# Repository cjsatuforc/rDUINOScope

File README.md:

# rDUINOScope

### ILI9488 3.5" SPI version: [buy pre-assembled kit](https://giacu92.bigcartel.com/product/rduinoscope-ili9488)
This rDUINOScope is an enanched version of the main release. The main differences are the following:

-  Uses ILI9488 480x320 px display in SPI, instead of HX8352B 400x240 px display, so bigger screen and less pin used. You can get a pre-assembled version in my [bigcartel shop](https://giacu92.bigcartel.com/product/rduinoscope-ili9488) or get yourself the 
ILI9488 display alone: [https://www.buydisplay.com/default/serial-spi-3-5-inch-tft-lcd-module-in-320x480-optl-touchscreen-ili9488](https://www.buydisplay.com/default/serial-spi-3-5-inch-tft-lcd-module-in-320x480-optl-touchscreen-ili9488)
-  Using AD7873 touch IC. Also compatibile with TSC2046/XPT2046 and ADS7843/AD7843 ICs. The software is able to detect and display any communications error with the touch IC.
-  Small code optimization to maximize speed (the ILI9488 supports only 24bit/px so it's quite slow as screen compared to HX... ones).
-  Joypad calibration at startup. No more panic to find the right values for the joypad.
-  Empirial March sound function moved to confirm good initialization of the device. If no sound then you're having problems! :'(
-  Automatic data and time set on clockScreen() derived from GPS data: the software is able to calculate the location's time zone and to auto update from summer or winter time.
-  Custom line of text can be appended to any .csv file to display custom "Description" strings. Example: I added "rich cluster with more than 100 stars" to M11 in messier.csv.
-  Changed color for Name and Description when tracking objects.
-  Different pin arrangement.
-  Options page settings such as tft brightness or sound state, are now saved onto the SD card and restored at each boot.
-  Added custom.csv wich can be used to add more custom sky objects.
-  Added pictures of all objects when tracking.

New features in development:
===========================================================
- Onboard touchscreen calibration
- Solar system objects tracking

## THE WORLD'S FIRST STAND ALONE ARDUINO BASED TELESCOPE CONTROL GOTO (handheld controller). 

rDUINOScope is an Open Source, Arduino Due based Telescope Control System (GOTO). Drafted as stand alone system, rDUINOScope does not need PC, Tablet or Cell Phone, nor Internet connection in order to operate and deliver stunning views! It does however supports Bluetooth and LX200 protocol to connect and be controlled by smart devices!

rDUINOScope uses database with THE BEST ~250 stellar objects ( Messier and Hidden Treasures Catalogues) and 200 stars, calculates their position on the sky and points the telescope. Implemented Alignment procedures allow for "Always in the eyepiece" experience when slewing to selected objects and once the object is in the eyepiece, the system keeps tracking it.

The best part of rDUINOScope is that it is an OPEN SOURCE SOFTWARE and HARDWARE! Few custom telescope makers have announced that they are adding or about to add it to their product line. In addition, few months ago a new HW shield board was born as a spin-off project to spare you the hassle of building your own rDUINOScope!

Published under GNU General Public License

Instructions on how to build hardware can be found on the project's website: http://rduinoscope.byethost24.com/
HACKADAY.IO Project: https://hackaday.io/project/21024-rduinoscope

Facebook: https://www.facebook.com/rDUINOScope/

# rDUINOScope _2.3.1_Boiana_EQ_Giacomo
===========================================================
Release date: 03 August 2017
Status: Stable Version
Author: Dessislav Gouzgounov / Десислав Гузгнов /(deskog@gmail.com) 
Edited: Giacomo Mammarella (giacomo.mammarella@student.univaq.it)

v2.3.1 aims to bring all existing hardware platforms into one code base. Additionally this version introduces new features to the rDUINOScope like Screensaver, TFT brightness, MosFET to control power to DRV8825 and etc.

Current release will also be used as a base to add the Alt/Az changes.

New features added in v2.3.1:
===========================================================
- Brings all existing flavours of the hardware to use same code!
- Hardware Changes!!! - Plese reffer to the HACKADAY instructions!
- Screen Brightness control;
- Screen Auto OFF function with timeout;
- Implemented FET transistor to control power to the stepper motors;
- More BlueTooth commands added to prepare for a screenless version (or operation);
- It is now possible to control rDUINOScope without the TFT screen - so called "BLIND" version.
- BUG fixes:
	- GPS fixes;
	- SlewTo speed issues for low amperage;

New features added in v2.3:
===========================================================
- Code Optimization for Performance (SlewTo now capable of speeds > 3 deg/sec);
- Added Celestial, Lunar and Solar tracking speeds;
- Added new Main Menu system for more functionality;
- Added control on 2 external devices (DEV 1 & 2 - you can hook your Heater, Fan and etc);
- Added support for SkySafari 5 (smartphone software);
- Added build in Star Atlas showing current telescope position;
- Shows current Firmware version on Loading screen and on Bluetooth request using LX200 protocol;
- Bug fixes:
	o Wrong DEC movement for negative DEC values passed over Bluetooth;
	o LST revised in the format XX:XX;

New features added in v2.1:
===========================================================
- Added “1 Star Alignment” Method;
- Added “Iterative Alignment” Method;
- Added 200 brightest stars to be used in alignment procedures;
- Added Bluetooth control from Stellarium (cloned LX200 communication protocols);
- Added Bluetooth connection with PC;
- Code has been refactored for easy reading/editing;
- Bug fixes:
	o Wrong DEC movement for negative DEC values;
	o Revised RA movement formula;
	o OnScreen messages have been fixed;
	o 1px. Buttons move after press event was fixed;

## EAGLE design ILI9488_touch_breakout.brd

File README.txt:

#rDUINOScope

ILI9488 SPI version:
	- Empirial March sound function moved after good initialization of the device.
      	- Auto data and time settings on clockScreen from GPS data: the software is able to calculate the location's time zone and to auto update to summer or winter time.
      	- Using AD7873 touch IC. Also compatibile with TSC2046/XPT2046 and ADS7843/AD7843 ICs. The software is able to detect and display any communications error with the touch IC.
	- Custom line of text can be appended to any .csv file to display custom "Description" strings. Example: I added "rich cluster with more than 100 stars" to M11 in messier.csv
      	- Changed color for Name and Description when tracking objects.
   	- Different pin arrangement
      	- Added custom.csv wich can be used to add more custom sky objects (still to be implemented)

THE WORLD'S FIRST STAND ALONE ARDUINO BASED TELESCOPE CONTROL GOTO (handheld controller). 

rDUINOScope is an Open Source, Arduino Due based Telescope Control System (GOTO). Drafted as stand alone system, rDUINOScope does not need PC, Tablet or Cell Phone, nor Internet connection in order to operate and deliver stunning views! It does however supports Bluetooth and LX200 protocol to connect and be controlled by smart devices!

rDUINOScope uses database with THE BEST ~250 stellar objects ( Messier and Hidden Treasures Catalogues) and 200 stars, calculates their position on the sky and points the telescope. Implemented Alignment procedures allow for "Always in the eyepiece" experience when slewing to selected objects and once the object is in the eyepiece, the system keeps tracking it.

The best part of rDUINOScope is that it is an OPEN SOURCE SOFTWARE and HARDWARE! Few custom telescope makers have announced that they are adding or about to add it to their product line. In addition, few months ago a new HW shield board was born as a spin-off project to spare you the hassle of building your own rDUINOScope!

Published under GNU General Public License

Instructions on how to build hardware can be found on the project's website: http://rduinoscope.byethost24.com/
HACKADAY.IO Project: https://hackaday.io/project/21024-rduinoscope

Facebook: https://www.facebook.com/rDUINOScope/

#rDUINOScope _2.3.1_Boiana_EQ_Giacomo
===========================================================
Release date: 03 August 2017
Status: Stable Version
Author: Dessislav Gouzgounov / Десислав Гузгнов /(deskog@gmail.com) 
Edited: Giacomo Mammarella (mammarella.g@gmail.com)

v2.3.1 aims to bring all existing hardware platforms into one code base. Additionally this version introduces new features to the rDUINOScope like Screensaver, TFT brightness, MosFET to control power to DRV8825 and etc.

Current release will also be used as a base to add the Alt/Az changes.

New features added in v2.3.1:
===========================================================
- Brings all existing flavours of the hardware to use same code!
- Hardware Changes!!! - Plese reffer to the HACKADAY instructions!
- Screen Brightness control;
- Screen Auto OFF function with timeout;
- Implemented FET transistor to control power to the stepper motors;
- More BlueTooth commands added to prepare for a screenless version (or operation);
- It is now possible to control rDUINOScope without the TFT screen - so called "BLIND" version.
- BUG fixes:
	- GPS fixes;
	- SlewTo speed issues for low amperage;

New features added in v2.3:
===========================================================
- Code Optimization for Performance (SlewTo now capable of speeds > 3 deg/sec);
- Added Celestial, Lunar and Solar tracking speeds;
- Added new Main Menu system for more functionality;
- Added control on 2 external devices (DEV 1 & 2 - you can hook your Heater, Fan and etc);
- Added support for SkySafari 5 (smartphone software);
- Added build in Star Atlas showing current telescope position;
- Shows current Firmware version on Loading screen and on Bluetooth request using LX200 protocol;
- Bug fixes:
	o Wrong DEC movement for negative DEC values passed over Bluetooth;
	o LST revised in the format XX:XX;

New features added in v2.1:
===========================================================
- Added “1 Star Alignment” Method;
- Added “Iterative Alignment” Method;
- Added 200 brightest stars to be used in alignment procedures;
- Added Bluetooth control from Stellarium (cloned LX200 communication protocols);
- Added Bluetooth connection with PC;
- Code has been refactored for easy reading/editing;
- Bug fixes:
	o Wrong DEC movement for negative DEC values;
	o Revised RA movement formula;
	o OnScreen messages have been fixed;
	o 1px. Buttons move after press event was fixed;

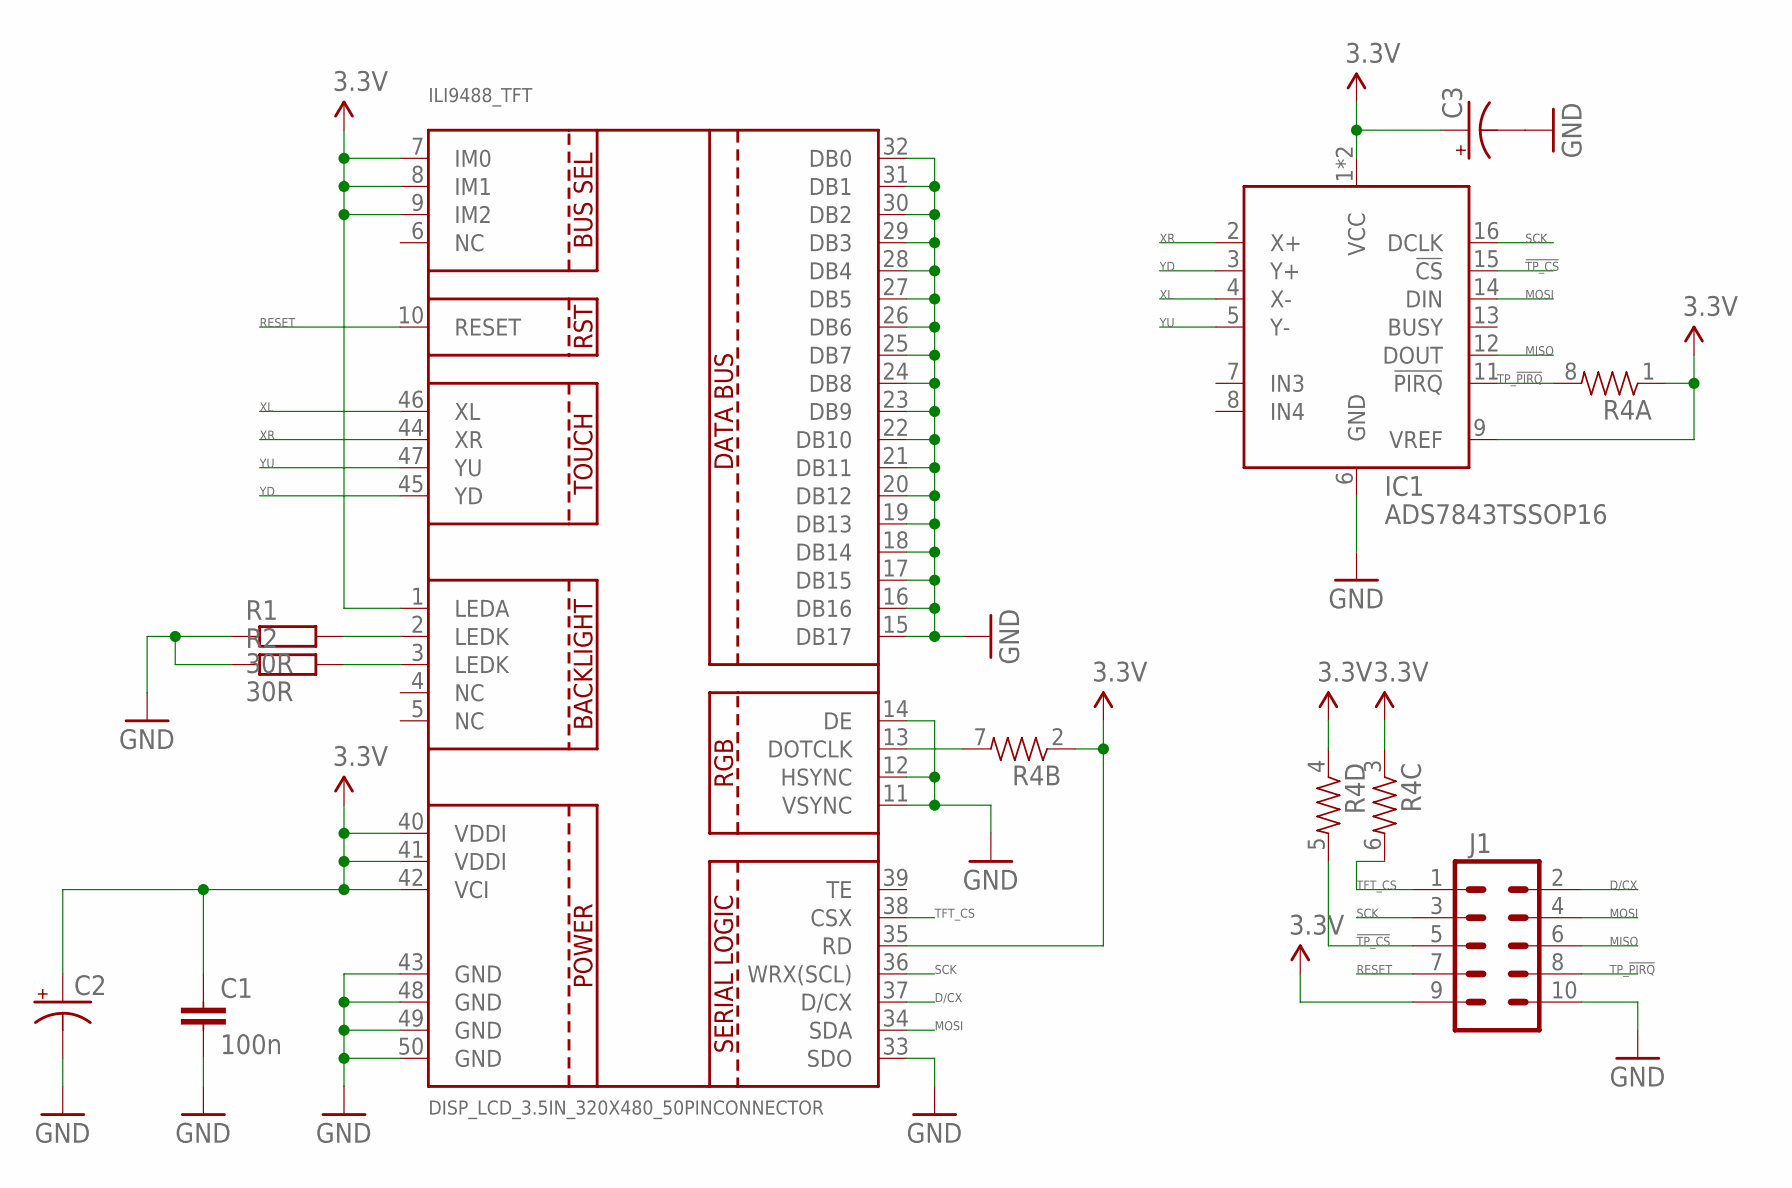
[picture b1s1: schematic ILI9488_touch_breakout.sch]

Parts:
C1: 100n; C0805K
C2, C3: CAPACITOR-POL0805; 0805A
IC1: ADS7843TSSOP16; TSSOP16
ILI9488_TFT: DISP_LCD_3.5IN_320X480_50PINCONNECTOR; TFT_3.5IN_50PIN_CONNECTOR
J1: M05X2PTH; AVR_ICSP
R1, R2: 30R; M0805
R4: RESISTOR-ARRAY0603-ARV; 0603-ARV

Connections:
3.3V: C1.1, C2.+, C3.+, IC1.1 (VCC), IC1.9 (VREF), IC1.10 (VCC), ILI9488_TFT.1 (LEDA), ILI9488_TFT.7 (IM0), ILI9488_TFT.8 (IM1), ILI9488_TFT.9 (IM2), ILI9488_TFT.35 (RD), ILI9488_TFT.40 (VDDI), ILI9488_TFT.41 (VDDI), ILI9488_TFT.42 (VCI), J1.9, R4.1, R4.2 (1), R4.3 (1), R4.4 (1)
!TP_CS: IC1.15 (!CS), J1.5, R4.5 (2)
D/CX: ILI9488_TFT.37 (D/CX), J1.2
GND: C1.2, C2.-, C3.-, IC1.6 (GND), ILI9488_TFT.11 (VSYNC), ILI9488_TFT.12 (HSYNC), ILI9488_TFT.14 (DE), ILI9488_TFT.15 (DB17), ILI9488_TFT.16 (DB16), ILI9488_TFT.17 (DB15), ILI9488_TFT.18 (DB14), ILI9488_TFT.19 (DB13), ILI9488_TFT.20 (DB12), ILI9488_TFT.21 (DB11), ILI9488_TFT.22 (DB10), ILI9488_TFT.23 (DB9), ILI9488_TFT.24 (DB8), ILI9488_TFT.25 (DB7), ILI9488_TFT.26 (DB6), ILI9488_TFT.27 (DB5), ILI9488_TFT.28 (DB4), ILI9488_TFT.29 (DB3), ILI9488_TFT.30 (DB2), ILI9488_TFT.31 (DB1), ILI9488_TFT.32 (DB0), ILI9488_TFT.33 (SDO), ILI9488_TFT.43 (GND), ILI9488_TFT.48 (GND), ILI9488_TFT.49 (GND), ILI9488_TFT.50 (GND), J1.10, R1.1, R2.1
MISO: IC1.12 (DOUT), J1.6
MOSI: IC1.14 (DIN), ILI9488_TFT.34 (SDA), J1.4
unnamed: ILI9488_TFT.2 (LEDK), R1.2
unnamed: ILI9488_TFT.3 (LEDK), R2.2
unnamed: ILI9488_TFT.13 (DOTCLK), R4.7 (2)
RESET: ILI9488_TFT.10 (RESET), J1.7
SCK: IC1.16 (DCLK), ILI9488_TFT.36 (WRX(SCL)), J1.3
TFT_CS: ILI9488_TFT.38 (CSX), J1.1, R4.6 (2)
TP_!PIRQ: IC1.11 (!PIRQ), J1.8, R4.8 (2)
XL: IC1.4 (X-), ILI9488_TFT.46 (XL)
XR: IC1.2 (X+), ILI9488_TFT.44 (XR)
YD: IC1.3 (Y+), ILI9488_TFT.45 (YD)
YU: IC1.5 (Y-), ILI9488_TFT.47 (YU)

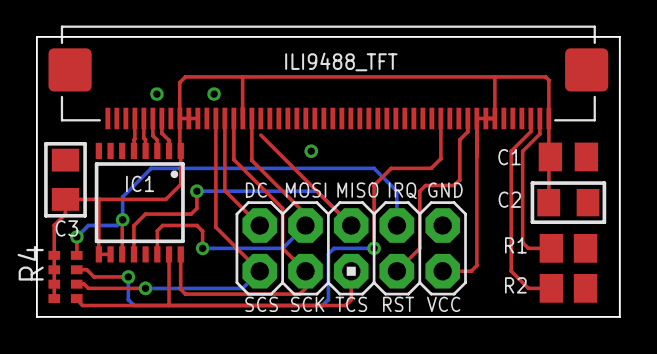
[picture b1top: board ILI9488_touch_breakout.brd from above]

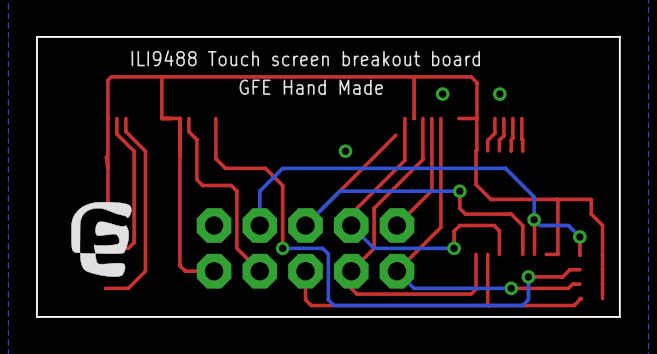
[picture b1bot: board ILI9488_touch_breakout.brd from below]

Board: 2 copper layers, 32.4 x 15.6 mm, 10 parts (2 on the bottom side), 17 nets.

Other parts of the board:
U$1: LOGO_PICCOLO

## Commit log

2017-09-14 ILI9488 adapted
2017-09-14 Difference between main
2017-09-17 starmap issue solved
2017-09-17 Resized images for 320x480
2017-09-17 custom.csv still in development
2017-09-17 Readme.txt
2017-09-17 TFT Breakout board
2017-09-17 Graphic update
2017-09-17 Pin change
2017-09-18 new functionality
2017-09-18 difference in this version
2017-09-18 Updates in the description
2017-09-19 Small fix
2017-09-19 Added joypad calibration
2017-09-19 new functions
2017-09-19 Supporters logo
2017-09-19 Joypad calibration and supporters logo
2017-09-19 TFT schematic and board layout
2018-01-08 board pics
2018-01-28 bug fix
2018-01-28 Bug fix
    Simple bug fix.
2018-01-28 Bugfix and update
2018-03-26 Auto-time fix
    Fixes a bug that causes false trigger of the summer_time time update
2018-03-30 updates
    Added reverse logic motor enable
    Enanched serial debug mode
    Fixed pin mismatch
    New Initialization graphics UNIX style
    Initialization failures check on DHT and RTC
    Auto summer time bug fix
2018-03-31 centered graphics and added logo
2018-04-04 upload functions.ino
    All functions moved here for fast debugging
2018-04-04 Store options on SD
    Now saves custom options and restores from sd at boot
2018-04-04 speed improvement
    Speed improvement on ILI9488 TFT
2018-04-04 Update README.md
    added options save
2018-04-06 Update pic
2018-04-07 board rendering
2018-04-07 Upload project libraries
2018-04-07 DMA TFT library translation
2018-07-31 bigcartel update
2018-08-03 implemented custom.csv
2018-08-03 grammar correction
2018-08-03 added ss_planet_names array
2018-08-03 custom.csv, moon tracking and touch functions
2018-08-03 images of objects
2018-08-03 small corrections
2018-08-03 objects bmps
2018-08-03 object bmps
2018-08-03 small bug fix and tft cal
2018-08-04 new pictures
2018-08-04 Sabit Yeşil Köroğlu's Messier images
    Thanks to Sabit Yeşil Köroğlu for providing all rescaled images
2018-08-04 sun tracking confirmation screen added
2018-08-04 added drawConfirmSunTrack
2018-08-04 touchscreen detection bug fix
2018-08-05 touchscreen cal bug fix
2018-08-05 sun calibration
2018-08-05 fixed grad symbol
2018-08-05 license
2018-08-05 new features in development
2018-08-07 update and fix planet calculations
2018-08-16 pics
2018-08-19 planet calculations released
2018-08-19 pwm on fans..in development
2018-08-19 battery level
2018-08-19 battery level and other bug fix
2018-08-20 planet calc
2018-08-20 battery calc
2018-08-20 added comments

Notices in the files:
parts and their libraries:
SparkFun-Connectors: Licensing: Creative Commons ShareAlike 4.0 International - https://creativecommons.org/licenses/by-sa/4.0
